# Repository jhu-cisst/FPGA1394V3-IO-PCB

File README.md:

# FPGA1394V3-IO-PCB

PCB design for I/O board used with [FPGA1394V3](https://github.com/jhu-cisst/FPGA1394V3), in KiCad format.

This board connects to the DF11 connector (J9) on FPGA1394V3, which provides +3.3V, GND and 4 I/O signals (MIO34-37) from the Zynq SoC PS, and makes protected versions of these signals available on a DB9F connector. Specifically, the +3.3V output has a 100 mA current limit and the I/O signals have 50 Ohm current-limiting resistors and a transorb (TVS diode) for protection.

This board is used in the [dVRK Si Controller](https://github.com/jhu-dvrk/dVRK-Si-Controller), starting with Rev 4 of the enclosure.

## DB9F Connector Pinout

## Files

* `dvrk-ios.kicad_pro`: KiCad project file
* `dvrk-ios.kicad_sch`: Schematics (KiCad format)
* `dvrk-ios.kicad_pcb`: PCB layout (KiCad format)
* `dvrk-ios-bom.xlsx`: Bill of Materials (Excel format)

## Subdirectories
(These are not required, since the symbols and footprints are already stored in the kicad_sch and kicad_pcb files)

* `3d`: 3D models of parts
* `DVRK.pretty`: Library of footprints (for PCB)
* `symbols`: Library of symbols (for schematics)

## Release Assets

* `dvrk-ios-schematics.pdf`: Schematics
* `dvrk-ios-pcb.zip`: Gerber files for PCB fabrication
* `dvrk-ios-assembly.zip`: Assembly files (BOM, CPL) for JLCPCB

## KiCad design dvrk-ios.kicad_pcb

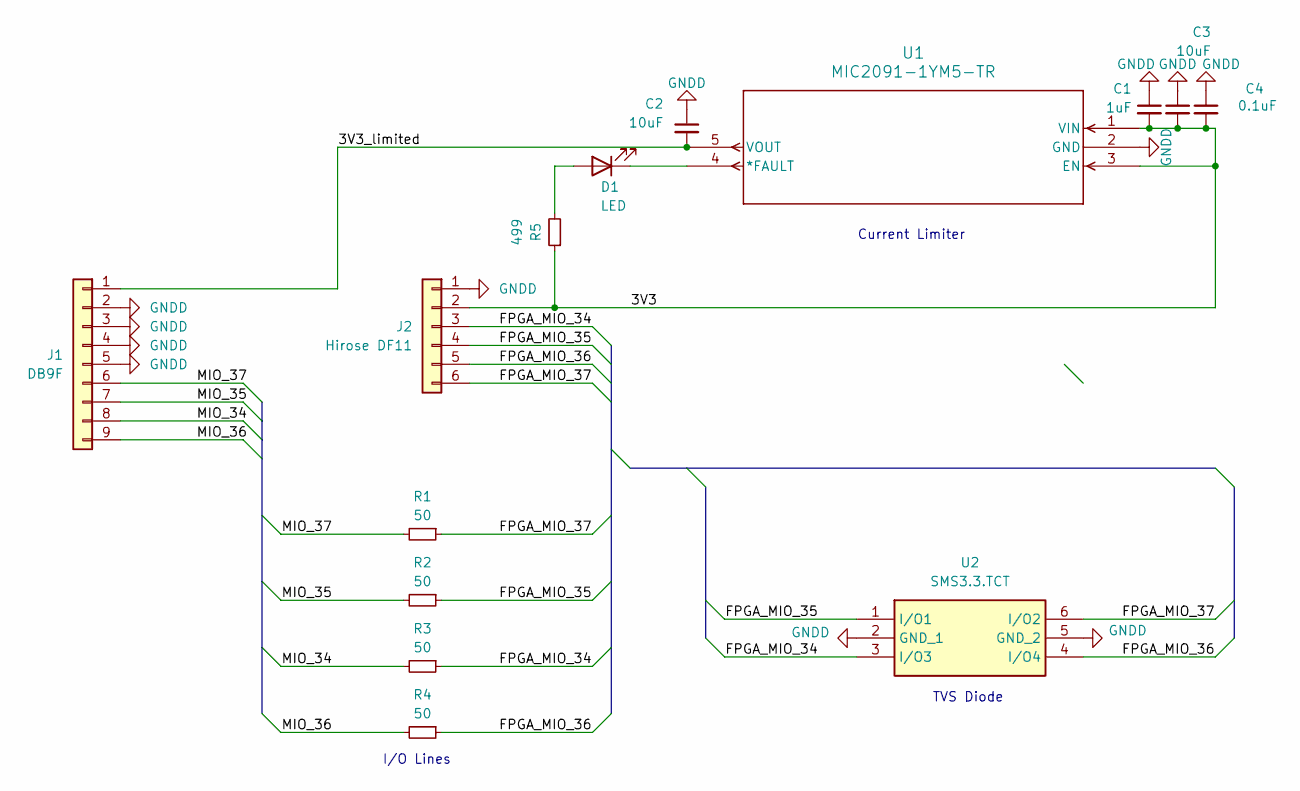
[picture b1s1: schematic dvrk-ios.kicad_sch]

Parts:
C1: 1uF; C_0603_1608Metric
C2, C3: 10uF; C_0603_1608Metric
C4: 0.1uF; C_0603_1608Metric
D1: LED; LED_LSM0805-2P0X1P25X0P8_VCC
J1: DB9F; 6E17C009SBF220
J2: Hirose DF11; SHDRRA6W60P200X200_2X3_800X1000X530P
R1, R2, R3, R4: 50; R_0603_1608Metric
R5: 499; R_0603_1608Metric
U1: MIC2091-1YM5-TR; SOT-23-5_M5_MCH
U2: SMS3.3.TCT; SOT95P280X145-6N; Mouser Part Number 947-SMS3.3.TCT

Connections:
/3V3: C1.2, C3.2, C4.2, J2.2, R5.1, U1.1 (VIN), U1.3 (EN)
/3V3_limited: C2.2, J1.1, U1.5 (VOUT)
/FPGA_MIO_34: J2.3, R3.1, U2.3 (I/O3)
/FPGA_MIO_35: J2.4, R2.1, U2.1 (I/O1)
/FPGA_MIO_36: J2.5, R4.1, U2.4 (I/O4)
/FPGA_MIO_37: J2.6, R1.1, U2.6 (I/O2)
/MIO_34: J1.8, R3.2
/MIO_35: J1.7, R2.2
/MIO_36: J1.9, R4.2
/MIO_37: J1.6, R1.2
GNDD: C1.1, C2.1, C3.1, C4.1, J1.2, J1.3, J1.4, J1.5, J2.1, U1.2 (GND), U2.2 (GND_1), U2.5 (GND_2)
unnamed: D1.2 (A), R5.2
unnamed: D1.1 (K), U1.4 (*FAULT)

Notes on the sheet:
I/O Lines
Current Limiter
TVS Diode

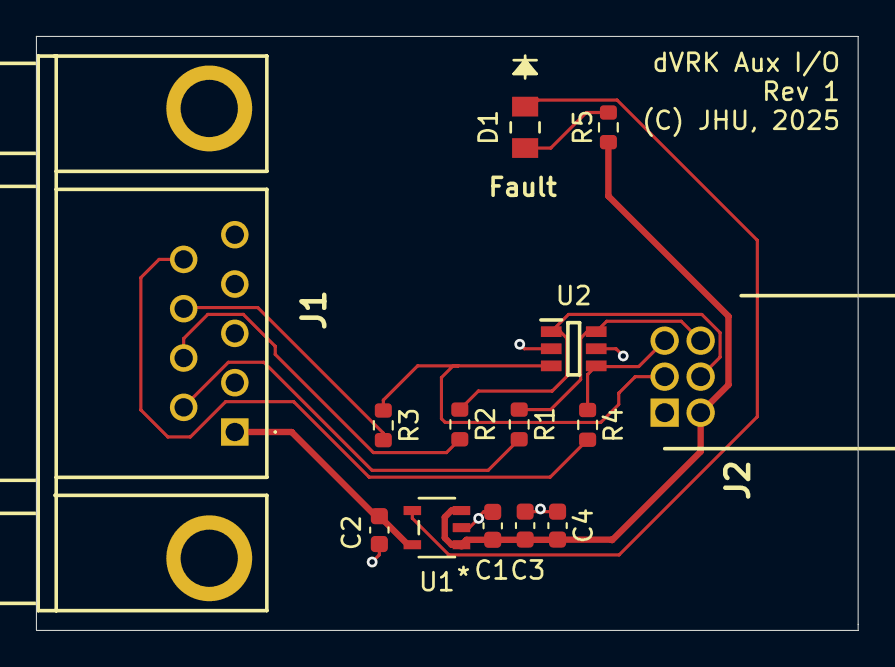
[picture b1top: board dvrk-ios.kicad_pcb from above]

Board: 2 copper layers, 45.7 x 33.0 mm, 14 parts (0 on the bottom side), 13 nets.

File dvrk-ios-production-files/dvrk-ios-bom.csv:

Comment,Designator,Footprint,LCSC Part Number
Hirose DF11,J2,SHDRRA6W60P200X200_2X3_800X1000X530P,C506666
10uF,C2,C_0603_1608Metric,C182375
SMS3.3.TCT,U2,SOT95P280X145-6N,C780132
50,R4,R_0603_1608Metric,C844932
50,R3,R_0603_1608Metric,C844932
1uF,C1,C_0603_1608Metric,C2167399
DB9F,J1,6E17C009SBF220,C17485936
LED,D1,LED_LSM0805-2P0X1P25X0P8_VCC,C17440976
50,R1,R_0603_1608Metric,C844932
MIC2091-1YM5-TR,U1,SOT-23-5_M5_MCH,C148025
0.1uF,C4,C_0603_1608Metric,C2181816
499,R5,R_0603_1608Metric,C2482478
10uF,C3,C_0603_1608Metric,C182375
50,R2,R_0603_1608Metric,C844932

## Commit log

2026-02-10 Added .gitignore
2026-02-10 Fixed README
2026-02-10 Added BOM to README
2026-02-10 Added BOM (Excel format)
2026-02-18 uploading updated files
2026-02-18 Added Excel BOM (had inadvertently been deleted)
2026-03-03 Removed production files from repository (move to Release Assets); BOM updates
2026-03-03 Minor update to README
2026-03-26 Added DB9F pinout
2026-03-26 Decreased size of pinout PNG
2026-03-26 Another image size change.
